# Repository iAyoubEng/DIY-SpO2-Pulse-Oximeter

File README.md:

# DIY SpO2 Pulse Oximeter

A custom-designed pulse oximeter built from scratch using KiCad 9.0.

## Overview

This project is a blood oxygen saturation (SpO2) and heart rate monitor, designed as a learning exercise in PCB design and embedded electronics.

## Hardware

| Component | Description |
|-----------|-------------|
| Arduino Nano v3.x | Microcontroller |
| MAX30102 | Pulse oximeter & heart-rate sensor (I2C) |
| SSD1306 | 0.96" OLED display (I2C) |
| Push button | User input |
| LEDs, resistors, capacitors | Supporting circuitry |

## PCB

- **4-layer board** (F.Cu, In1.Cu, In2.Cu, B.Cu)
- Custom footprints for the MAX30102 and SSD1306 modules
- Gerber files included, ready for fabrication

## Project Structure

```
├── learning.kicad_sch       # Schematic
├── learning.kicad_pcb       # PCB layout
├── learning.kicad_pro       # Project settings
├── spo2_stuff.kicad_sym     # Custom symbol library
├── spo2_stuff.pretty/       # Custom footprint library
├── gerbers/                 # Fabrication files
└── DIYSpo2_gerbers.zip      # Gerbers (zipped, fab-ready)
```

## Tools

- [KiCad 9.0](https://www.kicad.org/) — Schematic & PCB design

## License

This project is open source. Feel free to use it as a reference for your own designs.

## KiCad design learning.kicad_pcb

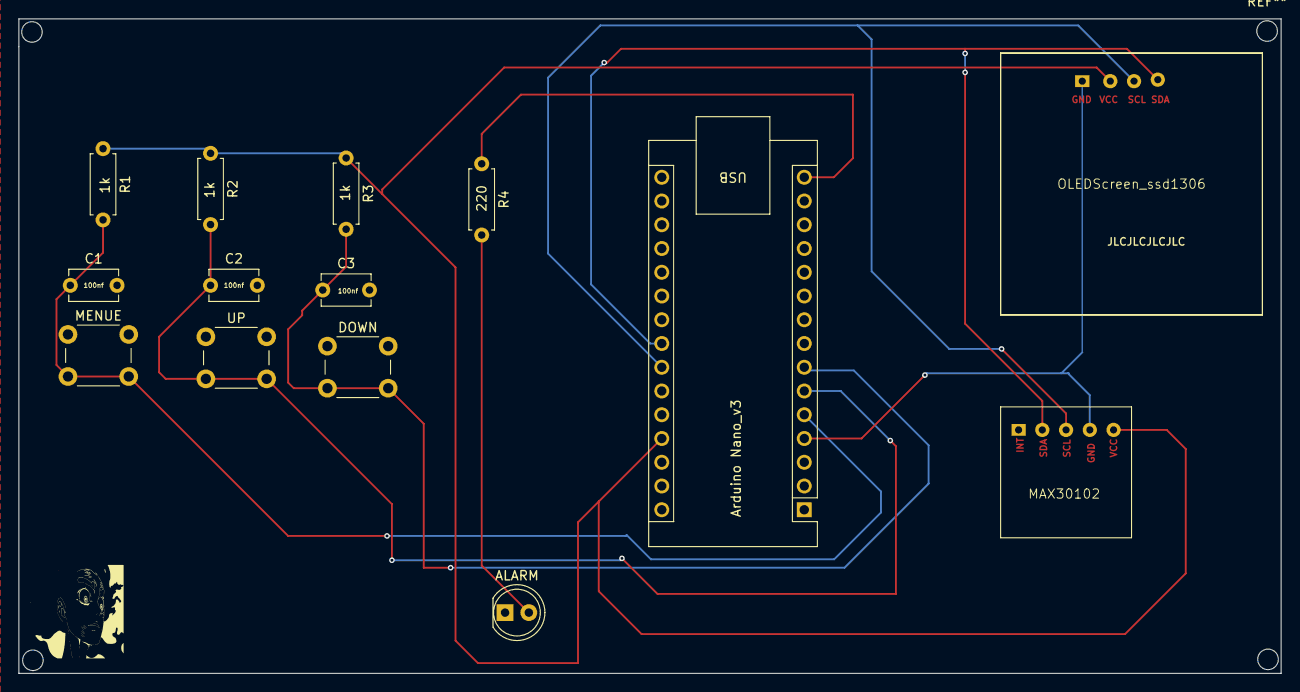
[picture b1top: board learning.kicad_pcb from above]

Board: 4 copper layers, 135.0 x 70.0 mm, 14 parts (0 on the bottom side), 9 nets.

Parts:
ALARM: LED; LED_D5.0mm
Arduino Nano_v3: Arduino Nano; Arduino_Nano
C1, C2, C3: 100n; C_Disc_D5.1mm_W3.2mm_P5.00mm
DOWN: SW_Push; SW_PUSH_6mm
MAX30102: MAX30102; MAX30102_module
MENUE: SW_Push; SW_PUSH_6mm
OLEDScreen_ssd1306: SSD1306_OledDisplay; SSD1306
R1, R2, R3: 1k; R_Axial_DIN0207_L6.3mm_D2.5mm_P7.62mm_Horizontal
R4: 220; R_Axial_DIN0207_L6.3mm_D2.5mm_P7.62mm_Horizontal
UP: SW_Push; SW_PUSH_6mm

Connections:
+5V: Arduino Nano_v3.27 (+5V), MAX30102.5 (VCC), OLEDScreen_ssd1306.2 (VCC), R1.1, R2.1, R3.1
GND: ALARM.1 (K), Arduino Nano_v3.4 (GND), Arduino Nano_v3.29 (GND), C1.2, C2.2, C3.2, DOWN.1, MAX30102.4 (GND), MENUE.1, OLEDScreen_ssd1306.1 (GND), UP.1
unnamed: Arduino Nano_v3.23 (A4), MAX30102.2 (SDA), OLEDScreen_ssd1306.4 (SDA)
unnamed: Arduino Nano_v3.24 (A5), MAX30102.3 (SCL), OLEDScreen_ssd1306.3 (SCL)
unnamed: Arduino Nano_v3.5 (D2), C1.1, MENUE.2, R1.2
unnamed: Arduino Nano_v3.6 (D3), C2.1, R2.2, UP.2
unnamed: Arduino Nano_v3.7 (D4), C3.1, DOWN.2, R3.2
unnamed: Arduino Nano_v3.15 (D12), R4.1
unnamed: ALARM.2 (A), R4.2
